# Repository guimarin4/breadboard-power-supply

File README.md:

# Breadboard Power Supply

A compact, dual-voltage linear power supply designed in **KiCad 9.0**, intended for electronics prototyping and breadboard applications.

The project converts a **12V DC input** into regulated **5V and approximately 3.3V outputs**, using LM7805 and LM317 linear voltage regulators.

The goal is to design a practical power supply while developing skills in electronic circuit design, schematic capture, PCB layout, and hardware prototyping.

## Project Overview

The power supply is designed to provide selectable voltage outputs for breadboards, microcontrollers, sensors, and other low-power electronic circuits.

### Main Features

- 12V DC input through a barrel jack connector
- ON/OFF power switch
- Fixed 5V output using the LM7805 voltage regulator
- Adjustable output targeting 3.3V using the LM317 voltage regulator
- LED power indicator
- Output voltage selection using jumper connectors
- Screw terminal connectors for external connections
- Common ground reference
- Through-hole components for easier assembly and soldering

## Technical Specifications

| Parameter | Description |
|---|---|
| Input voltage | 12V DC |
| Input connector | DC barrel jack |
| Voltage regulator 1 | LM7805 |
| Voltage regulator 2 | LM317 |
| Output voltage 1 | 5V DC |
| Output voltage 2 | ~3.3V DC (target) |
| Voltage selection | Jumper connectors |
| PCB design software | KiCad 9.0 |
| Assembly technology | Through-hole (THT) |
| Project status | In development |

**Note:** Maximum output current and thermal performance have not yet been validated.

## Circuit Design

The circuit is divided into three main sections.

### 1. Input and 5V Regulation

The circuit receives 12V DC through a barrel jack connector.

An ON/OFF switch controls the input power supplied to the voltage regulators.

The LM7805 converts the input voltage into a regulated 5V output.

Capacitors are used for input and output filtering, helping to reduce voltage fluctuations and electrical noise.

### 2. Adjustable 3.3V Regulation

The LM317 is an adjustable linear voltage regulator.

The resistor values are selected to obtain an output close to 3.3V.

Unlike the LM7805, which provides a fixed voltage, the LM317 allows different output voltages by modifying the resistor network.

### 3. Output Voltage Selection

The circuit includes jumper connectors to select the desired output voltage.

The intended configuration is:

| Jumper Position | Output Voltage |
|---|---|
| Pins 2–3 | 5V |
| Pins 1–2 | 3.3V |

Each output selection network must remain electrically independent to prevent shorting the two regulated outputs together.

## Main Components

| Component | Description |
|---|---|
| LM7805 | Fixed 5V linear regulator |
| LM317 | Adjustable linear regulator |
| DC Barrel Jack | 12V power input |
| Slide Switch | Main power switch |
| LED | Power indicator |
| Resistors | Voltage adjustment and LED current limiting |
| Capacitors | Filtering and decoupling |
| Pin Headers | Output voltage selection |
| Screw Terminals | External power connections |

## How to Open the Project

1. Install [KiCad](https://www.kicad.org/).
2. Clone this repository:

   ```bash
   git clone https://github.com/YOUR-USERNAME/breadboard-power-supply.git
   ```

3. Open `Breadboard_Power_Supply.kicad_pro`.
4. Use the Schematic Editor to inspect the circuit.
5. Use the PCB Editor to view or modify the board layout.

## Design Considerations

Because the project uses linear voltage regulators, part of the input power is dissipated as heat.

Thermal management, PCB layout, regulator operating limits, and component selection must be considered before hardware assembly.

The physical footprints must also be verified against the components selected for manufacturing.

## Tools

- **KiCad 9.0** — Schematic and PCB design
- **Git** — Version control
- **GitHub** — Project documentation and source management

## License

No license has been specified yet.

---

*Designed as a personal electronics engineering learning project.*

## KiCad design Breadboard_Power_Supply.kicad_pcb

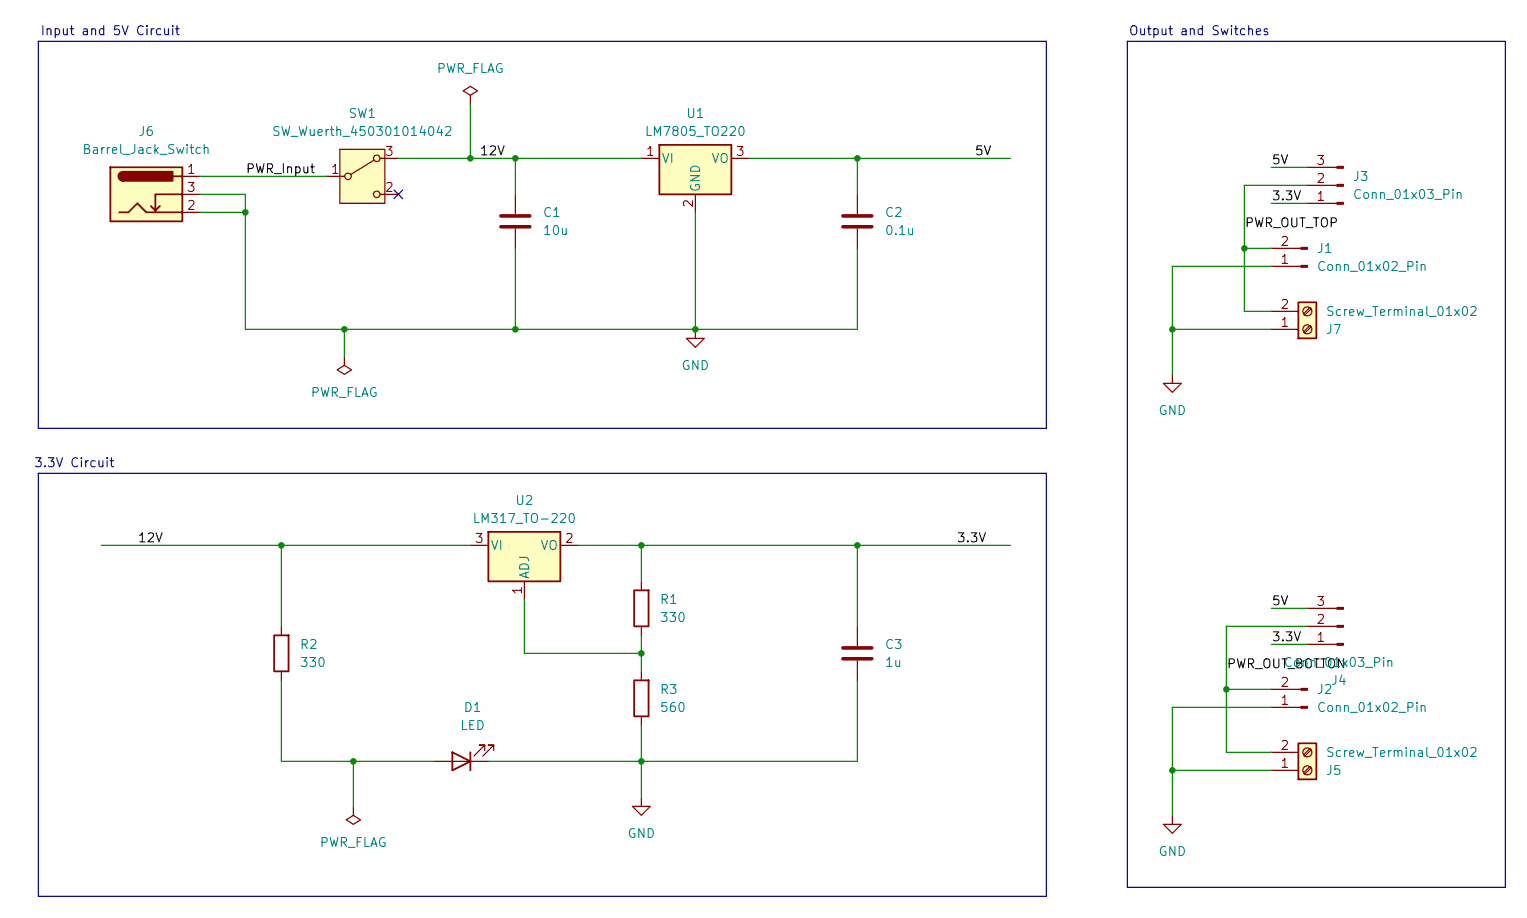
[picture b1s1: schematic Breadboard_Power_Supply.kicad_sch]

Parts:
C1: 10u; C_Disc_D3.0mm_W1.6mm_P2.50mm
C2: 0.1u; C_Disc_D3.0mm_W1.6mm_P2.50mm
C3: 1u; C_Disc_D3.0mm_W1.6mm_P2.50mm
D1: LED; LED_D5.0mm
J1, J2: Conn_01x02_Pin; PinHeader_1x02_P2.54mm_Vertical
J3, J4: Conn_01x03_Pin; PinHeader_1x03_P2.54mm_Vertical
J5, J7: Screw_Terminal_01x02; TerminalBlock_Phoenix_MKDS-1,5-2-5.08_1x02_P5.08mm_Horizont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
J6: Barrel_Jack_Switch; BarrelJack_Horizontal
R1, R2: 330; R_Axial_DIN0204_L3.6mm_D1.6mm_P7.62mm_Horizontal
R3: 560; R_Axial_DIN0204_L3.6mm_D1.6mm_P7.62mm_Horizontal
SW1: SW_Wuerth_450301014042; SW_Slide-03_Wuerth-WS-SLTV_10x2.5x6.4_P2.54mm
U1: LM7805_TO220; TO-220-3_Vertical
U2: LM317_TO-220; TO-220-3_Vertical

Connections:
/3.3V: C3.1, J3.1, J4.1, R1.2, U2.2 (VO)
/5V: C2.1, J3.3, J4.3, U1.3 (VO)
/12V: C1.1, R2.2, SW1.3 (A), U1.1 (VI), U2.3 (VI)
/PWR_Input: J6.1, SW1.1 (B)
/PWR_OUT_BOTTON: J2.2, J4.2, J5.2
/PWR_OUT_TOP: J1.2, J3.2, J7.2
GND: C1.2, C2.2, C3.2, D1.1 (K), J1.1, J2.1, J5.1, J6.2, J6.3, J7.1, R3.1, U1.2 (GND)
unnamed: D1.2 (A), R2.1
unnamed: R1.1, R3.2, U2.1 (ADJ)

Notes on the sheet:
3.3V Circuit
Output and Switches
Input and 5V Circuit

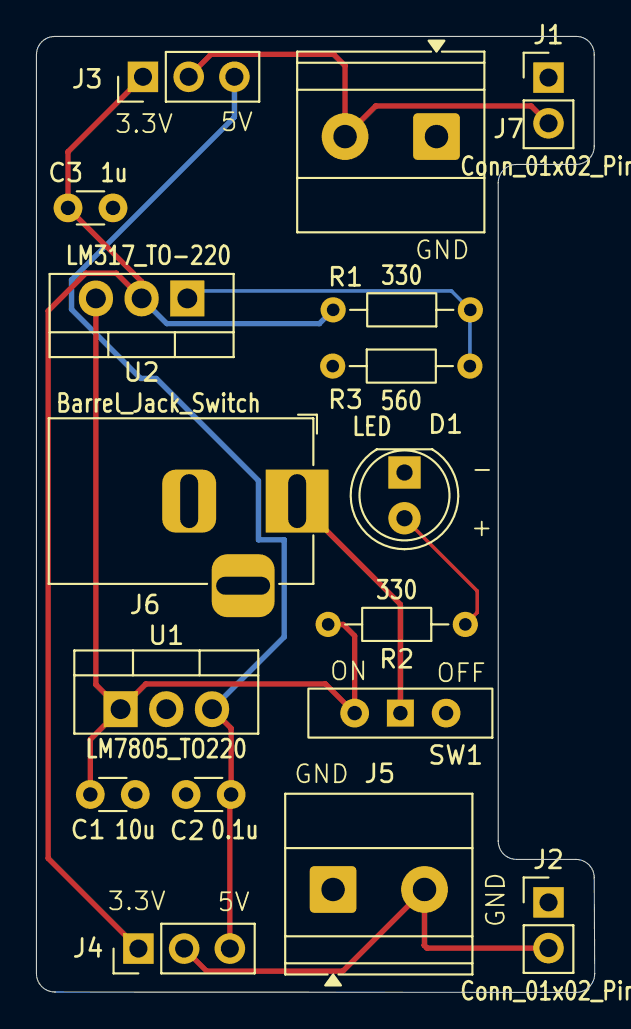
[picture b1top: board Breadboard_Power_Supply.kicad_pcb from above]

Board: 2 copper layers, 31.0 x 53.1 mm, 17 parts (0 on the bottom side), 9 nets.
